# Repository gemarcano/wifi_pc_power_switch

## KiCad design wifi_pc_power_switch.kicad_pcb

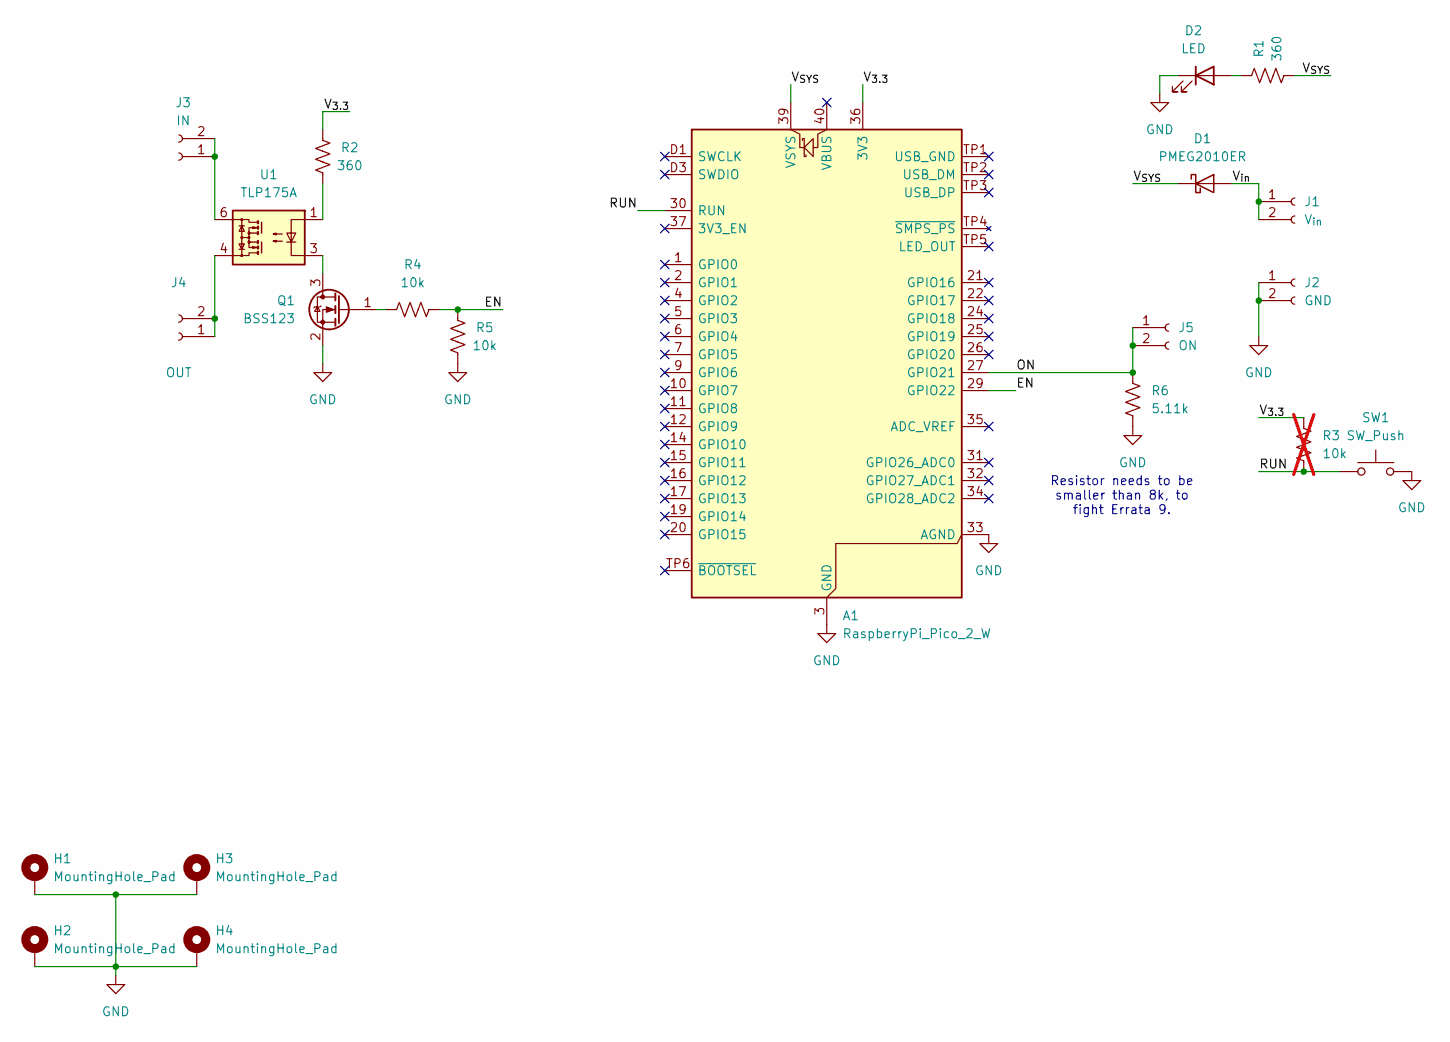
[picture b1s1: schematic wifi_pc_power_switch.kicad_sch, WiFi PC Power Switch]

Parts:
A1: RaspberryPi_Pico_2_W; RaspberryPi_Pico_W_Common_Unspecified; Digikey Product Number 2648-SC1633CT-ND
D1: PMEG2010ER; Nexperia_CFP3_SOD-123W
D2: LED; LED_0603_1608Metric_Pad1.05x0.95mm_HandSolder
H1, H2, H3, H4: MountingHole_Pad; MountingHole_3.2mm_M3_Pad_Via
J1: V_{in}; PinSocket_1x02_P2.54mm_Vertical
J2: GND; PinSocket_1x02_P2.54mm_Vertical
J3: IN; PinSocket_1x02_P2.54mm_Vertical
J4: OUT; PinSocket_1x02_P2.54mm_Vertical
J5: ON; PinSocket_1x02_P2.54mm_Vertical
Q1: BSS123; SOT-23
R1, R2: 360; R_0603_1608Metric_Pad0.98x0.95mm_HandSolder
R3: 10k; R_0603_1608Metric_Pad0.98x0.95mm_HandSolder; not fitted
R4, R5: 10k; R_0603_1608Metric_Pad0.98x0.95mm_HandSolder
R6: 5.11k; C_0603_1608Metric_Pad1.08x0.95mm_HandSolder
SW1: SW_Push; PTS636_SM50_SMTR_LFS
U1: TLP175A; MFSOP6-4_4.4x3.6mm_P1.27mm

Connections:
/EN: A1.29 (GPIO22), R4.2, R5.2
/ON: A1.27 (GPIO21), J5.1, J5.2, R6.1
/RUN: A1.30 (RUN), R3.2, SW1.1
/V_{3.3}: A1.36 (3V3), R2.2, R3.1
/V_{SYS}: A1.39 (VSYS), D1.1 (K), R1.1
/V_{in}: D1.2 (A), J1.1, J1.2
GND: A1.3 (GND), A1.8 (GND), A1.13 (GND), A1.18 (GND), A1.23 (GND), A1.28 (GND), A1.33 (AGND), A1.38 (GND), A1.D2 (GND), D2.1 (K), H1.1, H2.1, H3.1, H4.1, J2.1, J2.2, Q1.2 (S), R5.1, R6.2, SW1.2
unnamed: D2.2 (A), R1.2
unnamed: J3.1, J3.2, U1.6
unnamed: J4.1, J4.2, U1.4
unnamed: Q1.3 (D), U1.3
unnamed: Q1.1 (G), R4.1
unnamed: R2.1, U1.1

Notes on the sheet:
Resistor needs to be smaller than 8k, to fight Errata 9.

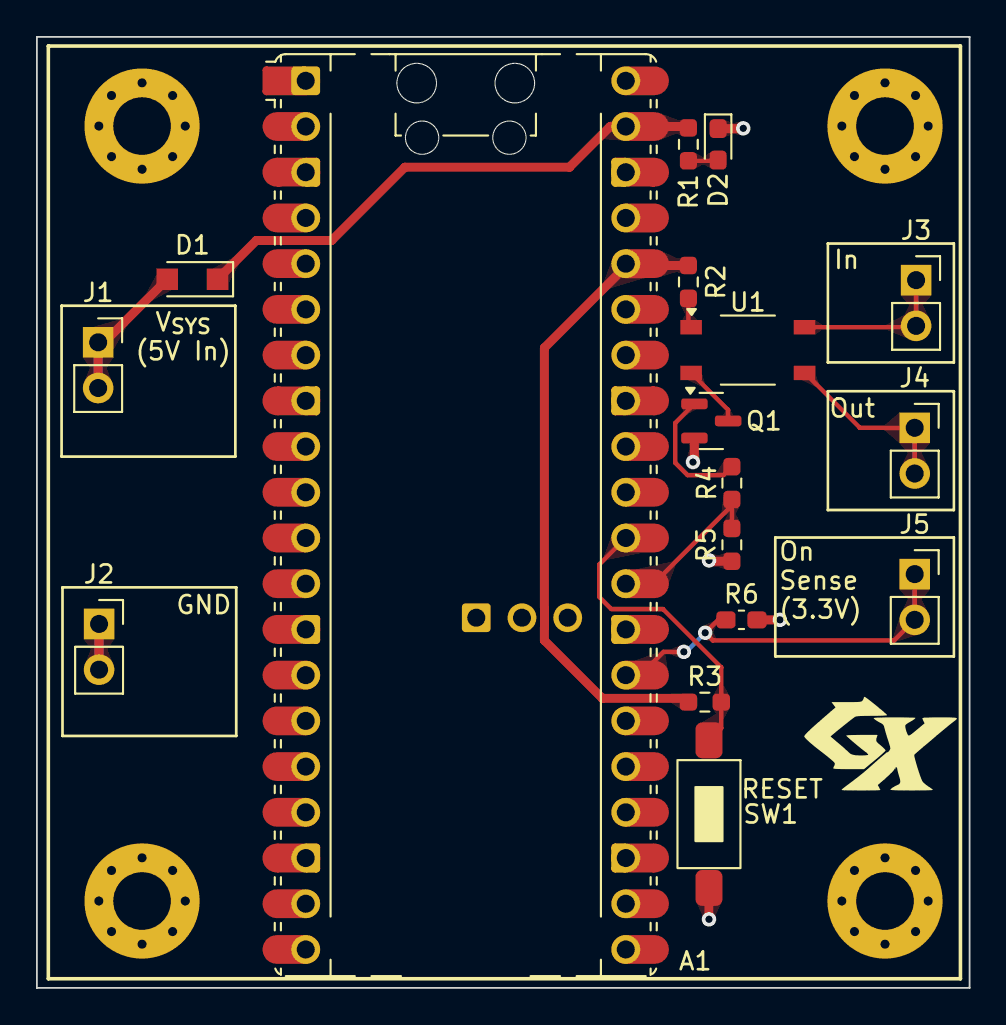
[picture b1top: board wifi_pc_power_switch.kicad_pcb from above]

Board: 2 copper layers, 51.8 x 52.8 mm, 21 parts (0 on the bottom side), 13 nets.

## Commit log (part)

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2023-11-09 Switch to using sockets API
2023-11-09 Added new blink task
    - With some basic communication between main task and blink task, basis
    of eventual turn PC on and off control
2023-11-17 Add pull-down to establish default switch state
    - Also force keep-out areas to be where they matter-- for USB and
    antenna, keep-out for both top and bottom layers. For test pads,
    keep-out only on top layer.
2023-12-07 Reorganize source directories
    - Initial GPIO implementation to control solid state relay
2023-12-09 Reorganize sources, add server support
2023-12-09 Split implementation from headers
    - Also split ntp_client out of main
2023-12-09 Add the option to set the hostname via cmake
2023-12-09 Remove NTP from main
    - This project doesn't really need NTP
2023-12-09 Add license information
    - Use new-ish SPDX-FileCopyrightText tag
2023-12-16 Better FreeRTOS malloc support
    - Turns out that for multi-thread malloc support we need to implement
    recursive locking of the malloc control structures through
    __malloc_lock and __malloc_unlock
    - Enable Newlib _reent support in FreeRTOS
    - Enable static allocation support in FreeRTOS
2023-12-20 Fix FreeRTOS malloc data initialization
    - Allow malloc locks to be initialized on demand, previous
    implementation ran into C++ static init fiasco
    - Update FreeRTOS Idle memory management to match latest upstream
    changes
2023-12-20 Fix file permissions
2023-12-23 Trivial CLI support, lwip status callbacks
    - Register trivial handlers to detect when lwip network status changes
    - Add a trivial CLI interface to toggle the switch over USB, and to
    query basic network state
2023-12-23 Add syslog support, cleanup init printing
    - Also, just move all initialization to the init_task-- it really just
    looks like with FreeRTOS the pico-sdk just makes too many assumptions
    that tasks, mutex/spinlocks, etc. are running inside tasks, so do the
    absolute bare minimum in main() to launch a FreeRTOS task.
2023-12-23 socket wrapper class, new namespace
    - Make new socket wrapper class, to handle closing automatically
    - Stick server and socket classes in new pc_remote_button namespace, to
    prevent clash with global namespace symbols
2023-12-23 Delete unused code, server.cpp
    - All of that code is in server.h now
2023-12-23 Move pc_switch to pc_remote_button namespace
2023-12-23 removed custom malloc protection, watchdog support
    - Turns out the pico-sdk is already doing locking through __wrap_malloc
    and friends. Something weird was going on that was causing a race
    between the two cores with my custom implementation, leading to a
    vListInsert looping forever because the node points to itself. I'm
    still not sure why this manifests (supposedly interrupt priority
    errors in Cortex-Ms are a usual suspect, as well as stack overflows).
2023-12-25 Add more error checking for networking
    - Loop server init and close in case of errors
2024-01-14 Move most output to log, track time in log
    - Status output now also prints logs
2024-01-14 Move switch into switch task
    - Ensure only switch task can control switch
2024-01-15 Replace snprintf with std::format
2024-01-15 Refactor out of main, use newlib errno
    - Refactor most tasks out of main.cpp, and isolate them as much as
    possible
    - switch_task exposes a global singleton to access the switch queue to
    pass switch times
    - Change copyright years
    - log exposes sys_log global log variable
2024-01-16 Log when switch is toggled
2024-01-16 Force a full reset if we fail initialization
2024-01-16 Improve handle_request move, shutup GCC format abi
    - Take socket by value forcing a move in handle_request, which also
    leads to automatic destruction of the object on function return as
    intended
    - add -Wno-psabi to shut up GCC from throwing up notices on std::format
    use
2024-01-17 Disable powersaving mode
    - Trying to improve reliability-- disable power saving in WiFi. We're
    plugged into main power so this should be fine. Doesn't seem to
    improve pings, though
2024-01-18 Trying to make wifi reconnect happen
    - In logs, I caught an event 6 hours in when the a lwip callback was
    called, and we lost our IP address. Try to force a disconnect and
    reconnect to refresh IP address
2024-02-05 Ensure power mode gets changed, more log output
    - Power mode change doesn't stick unless it happens after wifi is
    initialized, so move it to after we connect
    - Add more logging output when a change in link and status is detected
2024-02-06 A lot more debugging output for wifi state
    - Added RSSI and link state output to determine what's going wrong and
    when
    - Move power management after setting sta mode
    - fix bug in reconnect attempt, had inverted logic
2024-02-07 new wifi management task, lower priority of others
    - Lower the priority of all tasks I create to make sure network task is
    prioritized
    - Dedicated wifi management task that monitors every second for changes
    to link status, since apparently there can be some changes that
    aren't detected by the driver/pico-sdk network layers
    - tweak logging output to make it easier to figure out who's printing
2024-02-19 wifi: move from main, check lwip flags also
    - Apparently checking pico cyw43 status isn't enough-- it always
    returns JOIN even if lwip reports a link change/drop. Also check LWIP
    flag and try to reconnect if we lose the link.
2024-02-20 Remove socket debug logging
    - I'm pretty sure the basic socket construction logic works now, remove
    the logging. In the future, we may want to extend logging to have
    different levels.
2024-02-21 Multicore watchdog support
    - Use a central watchdog task to aggregate the state of another two
    tasks to determine whether to pet the watchdog or not.
2024-03-11 Add .gitignore with KiCAD information
2024-03-12 Add pcrb namespace, use last code from sctu
    - Copy the latest networking code from snes_controllers_to_usb project,
    before I removed it from that directory (I really should make a pico
    library of my stuff).
    - Move almost everything to the pcrb (pc_remote_button) namespace.
    - Also copied latest watchdog code from sctu.
    - Updated to use xTaskCreateAffinitySet instead of xTaskCreate.
2024-03-14 Add MPU support, fix kill/reboot commands
    - Add MPU support, blocking access to the first 256 bytes of memory to
    catch null-pointer dereferences. This breaks USB auto-reboot,
    however...
    - Fix kill command by increasing the max length of the task names, and
    using the right name to kill one of the watchdog tasks.
    - Fix the reboot command by disabling the MPU before issuing a usb
2024-03-14 Remove MPU code, breaks rp2040 bootrom funcs
    - rp2040 bootrom has functions in bootrom, which starts at address 0x0.
    One of these is the usb reset function, used by cli "r" command and
    by the pico-sdk's vendor reboot interface. While I can disable the
    MPU in my code, I can't do the same for pico-sdk's without patching
    it, or without taking over tinyusb, so just disable the MPU.
2024-06-22 Pull in gpico library
    - gpico library provides syscalls for IO, but requires some USB
    plumbing (maybe I should have it provide said plumbing?). Add
    plumbing in main
    - gpico takes care of watchdogs, and provides auxiliary FreeRTOS
    functions. Beware, it is opinionated and expects Heap4
    implementation.
2024-06-30 Preliminary grub control support
    - Expose a FAT12 FS that GRUB can read to change the default option for
    booting
2024-11-13 Update for pico-sdk version 2
2024-11-15 Don't wait for CDC, halt FreeRTOS for programming
    - Don't wait until we get a CDC connection to start everything up...
    that requires someone to connect over serial
    - For some reason trying to switch to programming boot mode is hanging
    sometimes. I think it's because it relies on a watchdog firing, and
    if the right FreeRTOS task stays alive constantly petting the
    watchdog, the reset will never happen. As such, for reboot, halt the
2024-11-22 Tweak task priorities to avoid starvation
    - CLI and USB tasks are very time hungry, and not super extremely time
    sensitive, so reduce their priority below other things. Also, it
    looks like the Pico SDK FreeRTOS support hard-codes some TCP tasks to
    a priority of IDLE+1, so be mindful of not starving those either.
2024-11-25 Use TinyUSB FreeRTOS support, set board to pico_w
    - Hard-code board type to pico_w because that's all we support
    - By default TinyUSB uses Pico OS baremetal support with the pico-sdk
    (I'm guessing locking and what-have-you). Use FreeRTOS instead,
    especially since we're not using pico-sdk stdout implementation
    anyway
2024-11-26 Revision B*: Tentative making everything denser
    - Added 5V notification LED, so it's easier to tell when the board is
    actually powered
    - Condensed the board appreciably
2024-11-28 Remove autotools notice in LICENSE
    - We're not using autotools in this project
2025-05-29 Update to work with latest gpico changes
    - gpico now manages USB task loop
2025-06-24 Add preliminary pico interface reboot support
2025-06-24 Use new gpico reset functions
    - except for baud method, just in case for now
2025-06-25 Improve handle_request
    - handle_request no longer assumes 4 bytes input, it assumes 2 bytes
    first, stating how much to read afterwards, up to 64 bytes.
    - adjusted the rest of the network_task to use this new functionality,
    and fixed a bug in what std::expected to actually be using (should
    use the handle_request one, not the accept one)
2025-07-09 We don't need that many pins, add sense
    - Reduce the 4x pins to 2x, and place them near the edge (to be used
    with simple screw terminals)
    - Add a sense line, so the MCU can tell if the computer is on. It needs
    a pulldown due to rp2350 E9 errata.
2025-07-10 Add new monitor task
    - Monitor task monitors the PC power state through pin 21. This pin
    should be connected to one of the 3.3V power pins on the ATX
    motherboard connector (or any other 3.3V pin on the motherboard).
2025-07-10 server: allow for 1024 max size payload
    - Also, better handling of incomplete transfer
2025-07-10 server: let user allocate recv storage
2025-07-12 Split commands from CLI
    - This is in preparation to allowing CLI access over the network
    - There's something wrong with the way printf is working-- it seems to
    hang the cli task somehow? Need to dig into it
2025-07-12 Increase stack switch task, up priority for cli
    - Switch task apparently was running out of memory
    - Something (not sure what, yet) was starving the CLI task out of time.
    Up the priority to match everything else.
2025-07-12 Fixed USB starving tasks, add priority to status
    - gpico fixes USB task starving all others by delaying by one tick
    (need to figure out why the FreeRTOS blocking isn't being used)
    - Add priority to status printout for each task
2025-07-12 network: add magic to header, add socket timeout
2025-07-13 network: Add scaffolding for request type
2025-07-13 network: reply
2025-07-13 network and cli: support for changing boot select
    - Things are getting a bit nasty, need to think about how to clean up
2025-07-13 request_handler: refactor out of server
    - Make a class to manage reading and sending data, let server manage
    incoming connections
2025-07-13 network: improving error messages
2025-07-14 network: support for sensing power
    - Allows query of 3.3V PC rail over pin 21 over network
    - Fixed bug with timing of network toggle parameter sent to switch task
2025-07-21 more WIP, actually getting responses from server now
2025-07-22 Improve MQTT handling
    - Had to increase stack size for lwip thread
2025-07-28 Helper functions for DNS, also expose DNS on CLI
2025-07-29 Add dns documentation, tweak stack usage
2025-07-29 Improve mqtt, fix warnings
2025-08-03 mqtt: make more functions blocking
    - make connect and new function subscribe block until callbacks
    indicate either success or failure
